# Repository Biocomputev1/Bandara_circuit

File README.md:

# Bandara_circuit
This the Bandara circuit kicad repository

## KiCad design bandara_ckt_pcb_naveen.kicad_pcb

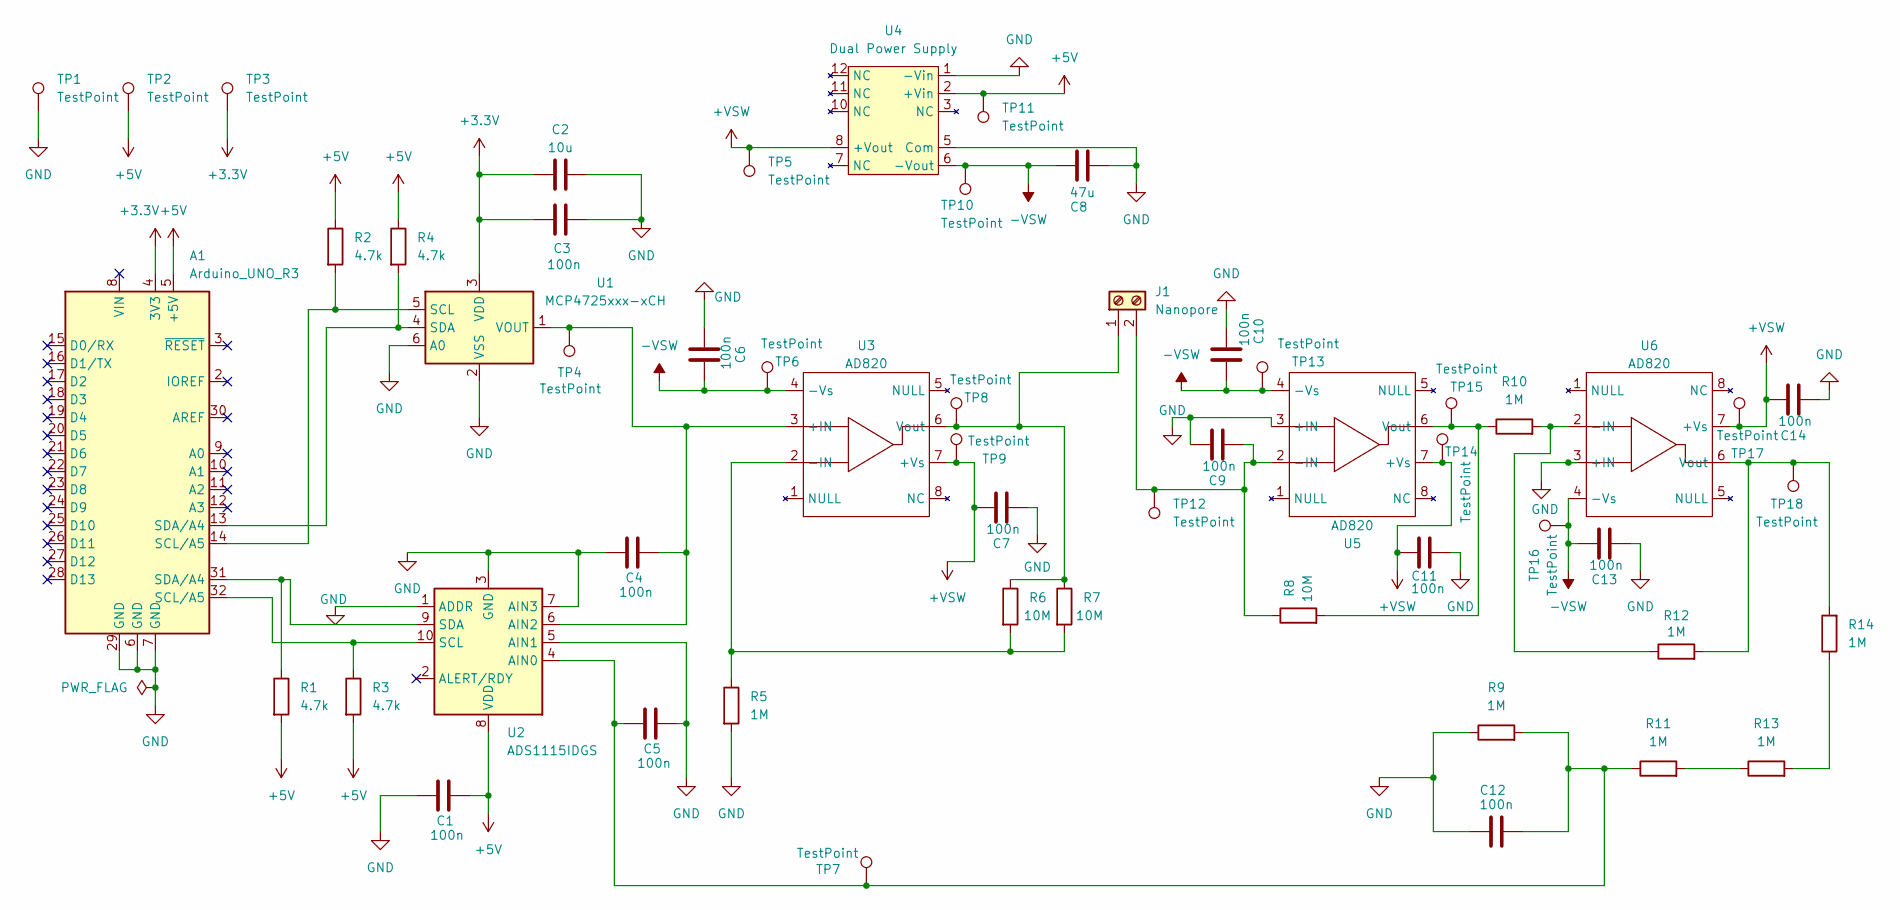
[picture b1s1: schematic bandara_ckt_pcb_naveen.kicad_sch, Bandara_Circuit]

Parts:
A1: Arduino_UNO_R3
C1, C3, C4, C5, C6, C7, C9, C10, C11, C12, C13, C14: 100n; C_0805_2012Metric_Pad1.18x1.45mm_HandSolder
C2: 10u; CP_EIA-3216-10_Kemet-I
C8: 47u; C_Radial_D8.0mm_H11.5mm_P3.50mm
J1: Nanopore; PHOENIX_1935161
R1, R2, R3, R4: 4.7k; R_0603_1608Metric_Pad0.98x0.95mm_HandSolder
R5, R9, R10, R11, R12, R13, R14: 1M; R_0603_1608Metric_Pad0.98x0.95mm_HandSolder
R6, R7, R8: 10M; R_0603_1608Metric_Pad0.98x0.95mm_HandSolder
TP1, TP2, TP3, TP4, TP5, TP6, TP7, TP8, TP9, TP10, TP11, TP12, TP13, TP14, TP15, TP16, TP17, TP18: TestPoint; TestPoint_THTPad_D2.0mm_Drill1.0mm
U1: MCP4725xxx-xCH; SOT-23-6
U2: ADS1115IDGS; TSSOP-10_3x3mm_P0.5mm
U3, U5, U6: AD820; N_8_ADI
U4: Dual Power Supply; NDU05

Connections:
+3.3V: A1.4 (3V3), C2.1, C3.1, TP3.1, U1.3 (VDD)
+5V: A1.5 (+5V), C1.2, R1.2, R2.1, R3.2, R4.1, TP2.1, TP11.1, U2.8 (VDD), U4.2 (+Vin)
+VSW: C7.2, C11.1, C14.2, TP5.1, TP9.1, TP14.1, TP17.1, U3.7 (+Vs), U4.8 (+Vout), U5.7 (+Vs), U6.7 (+Vs)
-VSW: C6.2, C8.1, C10.2, C13.2, TP6.1, TP10.1, TP13.1, TP16.1, U3.4 (-Vs), U4.6 (-Vout), U5.4 (-Vs), U6.4 (-Vs)
GND: A1.6 (GND), A1.7 (GND), A1.29 (GND), C1.1, C2.2, C3.2, C4.1, C5.2, C6.1, C7.1, C8.2, C9.2, C10.1, C11.2, C12.1, C13.1, C14.1, R5.2, R9.1, TP1.1, U1.2 (VSS), U1.6 (A0), U2.1 (ADDR), U2.3 (GND), U2.5 (AIN1), U2.7 (AIN3), U4.1 (-Vin), U4.5 (Com), U5.3 (+IN), U6.3 (+IN)
unnamed: J1.1, R6.1, R7.1, TP8.1, U3.6 (Vout)
unnamed: C9.1, J1.2, R8.1, TP12.1, U5.2 (-IN)
unnamed: R11.2, R13.1
unnamed: R13.2, R14.1
unnamed: A1.14 (SCL/A5), R2.2, U1.5 (SCL)
unnamed: A1.13 (SDA/A4), R4.2, U1.4 (SDA)
unnamed: C4.2, TP4.1, U1.1 (VOUT), U2.6 (AIN2), U3.3 (+IN)
unnamed: C5.1, C12.2, R9.2, R11.1, TP7.1, U2.4 (AIN0)
unnamed: A1.32 (SCL/A5), R3.1, U2.10 (SCL)
unnamed: A1.31 (SDA/A4), R1.1, U2.9 (SDA)
unnamed: R5.1, R6.2, R7.2, U3.2 (-IN)
unnamed: R8.2, R10.1, TP15.1, U5.6 (Vout)
unnamed: R10.2, R12.1, U6.2 (-IN)
unnamed: R12.2, R14.2, TP18.1, U6.6 (Vout)

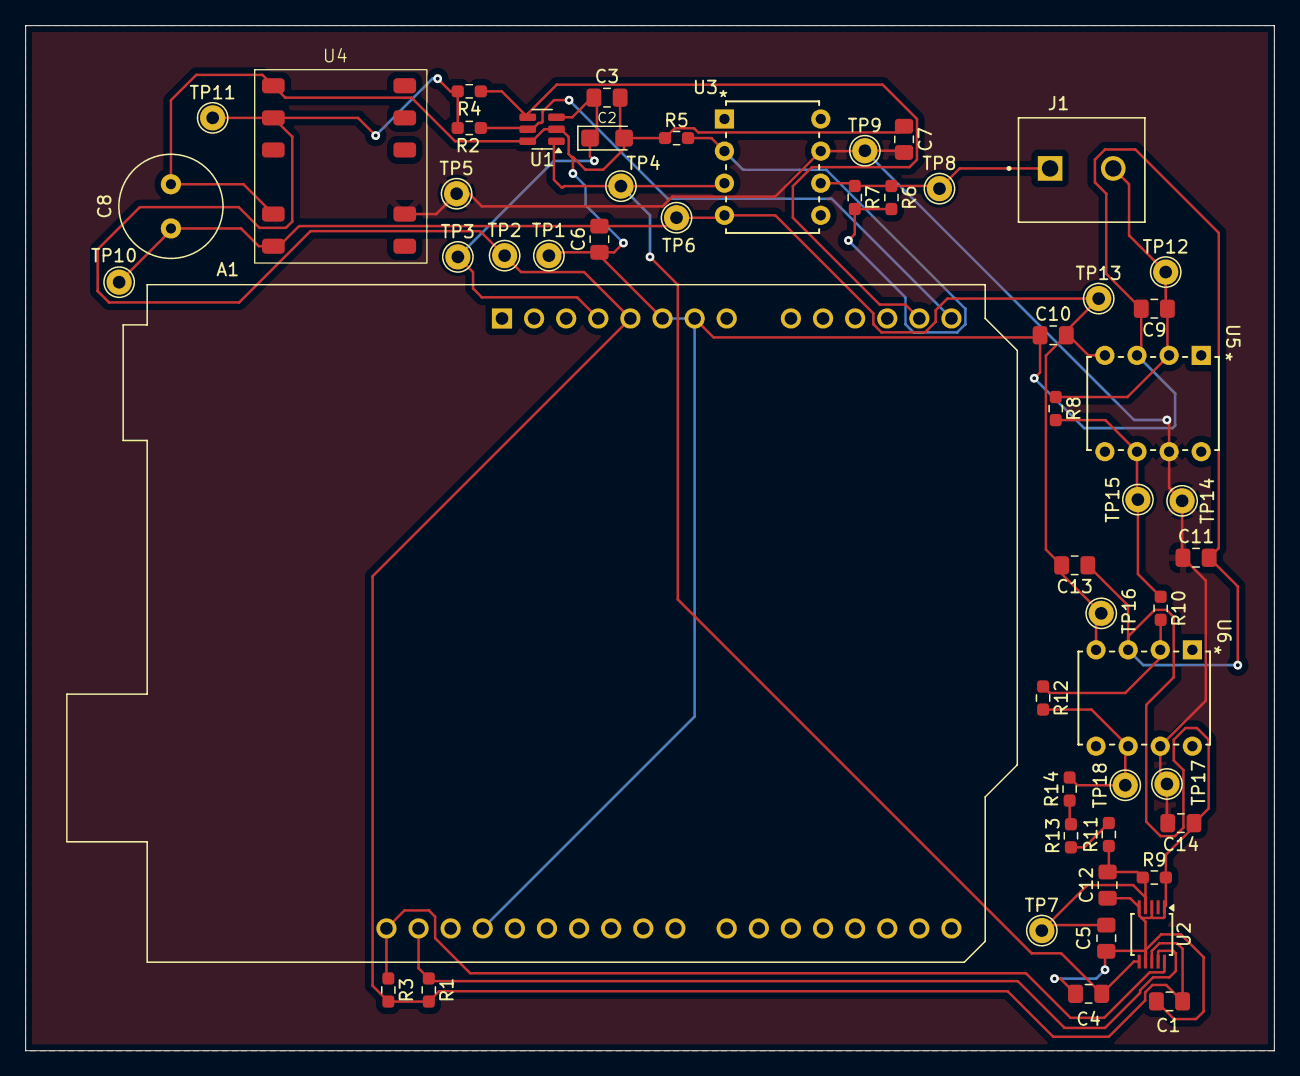
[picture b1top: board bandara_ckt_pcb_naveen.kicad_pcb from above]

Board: 2 copper layers, 98.8 x 81.1 mm, 54 parts (0 on the bottom side), 19 nets.

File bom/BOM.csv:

Reference,Value,Datasheet,Footprint,Qty,DNP
A1,Arduino_UNO_R3,https://www.arduino.cc/en/Main/arduinoBoardUno,Module:Arduino_UNO_R3,1,5
"C1,C3,C4,C5,C6,C7,C9,C10,C11,C12,C13,C14",100n,~,Capacitor_SMD:C_0805_2012Metric_Pad1.18x1.45mm_HandSolder,12,60
C2,10u,~,Capacitor_Tantalum_SMD:CP_EIA-3216-10_Kemet-I,1,5
C8,47u,~,Capacitor_THT:C_Radial_D8.0mm_H11.5mm_P3.50mm,1,5
J1,Nanopore,~,bandara_ckt_footprints:PHOENIX_1935161,1,5
"R1,R2,R3,R4",4.7k,~,Resistor_SMD:R_0603_1608Metric_Pad0.98x0.95mm_HandSolder,4,20
"R5,R9,R10,R11,R12,R13,R14",1M,~,Resistor_SMD:R_0603_1608Metric_Pad0.98x0.95mm_HandSolder,7,35
"R6,R7,R8",10M,~,Resistor_SMD:R_0603_1608Metric_Pad0.98x0.95mm_HandSolder,3,15
"TP1,TP2,TP3,TP4,TP5,TP6,TP7,TP8,TP9,TP10,TP11,TP12,TP13,TP14,TP15,TP16,TP17,TP18",TestPoint,~,TestPoint:TestPoint_THTPad_D2.0mm_Drill1.0mm,18,90
U1,MCP4725xxx-xCH,http://ww1.microchip.com/downloads/en/DeviceDoc/22039d.pdf,Package_TO_SOT_SMD:SOT-23-6,1,5
U2,ADS1115IDGS,http://www.ti.com/lit/ds/symlink/ads1113.pdf,Package_SO:TSSOP-10_3x3mm_P0.5mm,1,5
"U3,U5,U6",AD820,,bandara_ckt_footprints:N_8_ADI,3,15
U4,Dual Power Supply,,NDU_SMD:NDU05,1,5
,,,,,
COMPONENTS TO PROCURE,,,,,
C2,10u,~,Capacitor_Tantalum_SMD:CP_EIA-3216-10_Kemet-I,1,5
R12,1M,~,Resistor_SMD:R_0603_1608Metric_Pad0.98x0.95mm_HandSolder,1,5
C3,100n,~,Capacitor_SMD:C_0805_2012Metric_Pad1.18x1.45mm_HandSolder,1,5

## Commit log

2025-04-16 Intial commit
2025-04-16 Review version of Bandara circuit
2025-04-16 fixed some PCB thing
2025-04-16 The Required correction is done
2025-04-17 Regular Commit
2025-04-18 PCB and Schematic updated after YES from Bandara
2025-04-18 Plotter Gerber, Production Version
2025-04-20 Final before check
2025-04-21 Final version pushed to production
2025-04-21 Final commit after changing C2 footprint
2025-04-23 BOM file is modified
